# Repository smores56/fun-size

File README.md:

Fun Size
========

The Fun Size is an ergonomic keyboard PCB. With 32 to 36 keys, it uses Kailh hotswap sockets to
support Choc v1 switches, in addition to up to 4 EVQWGD001 horizontal rotary encoders.

The first version has had prototypes ordered for testing and depiction here using the
[gerber archive][./v1/fun-size.zip] saved in this repo. Once it arrives, pictures will be uploaded
here.

Check back later for QMK configuration to run your own.

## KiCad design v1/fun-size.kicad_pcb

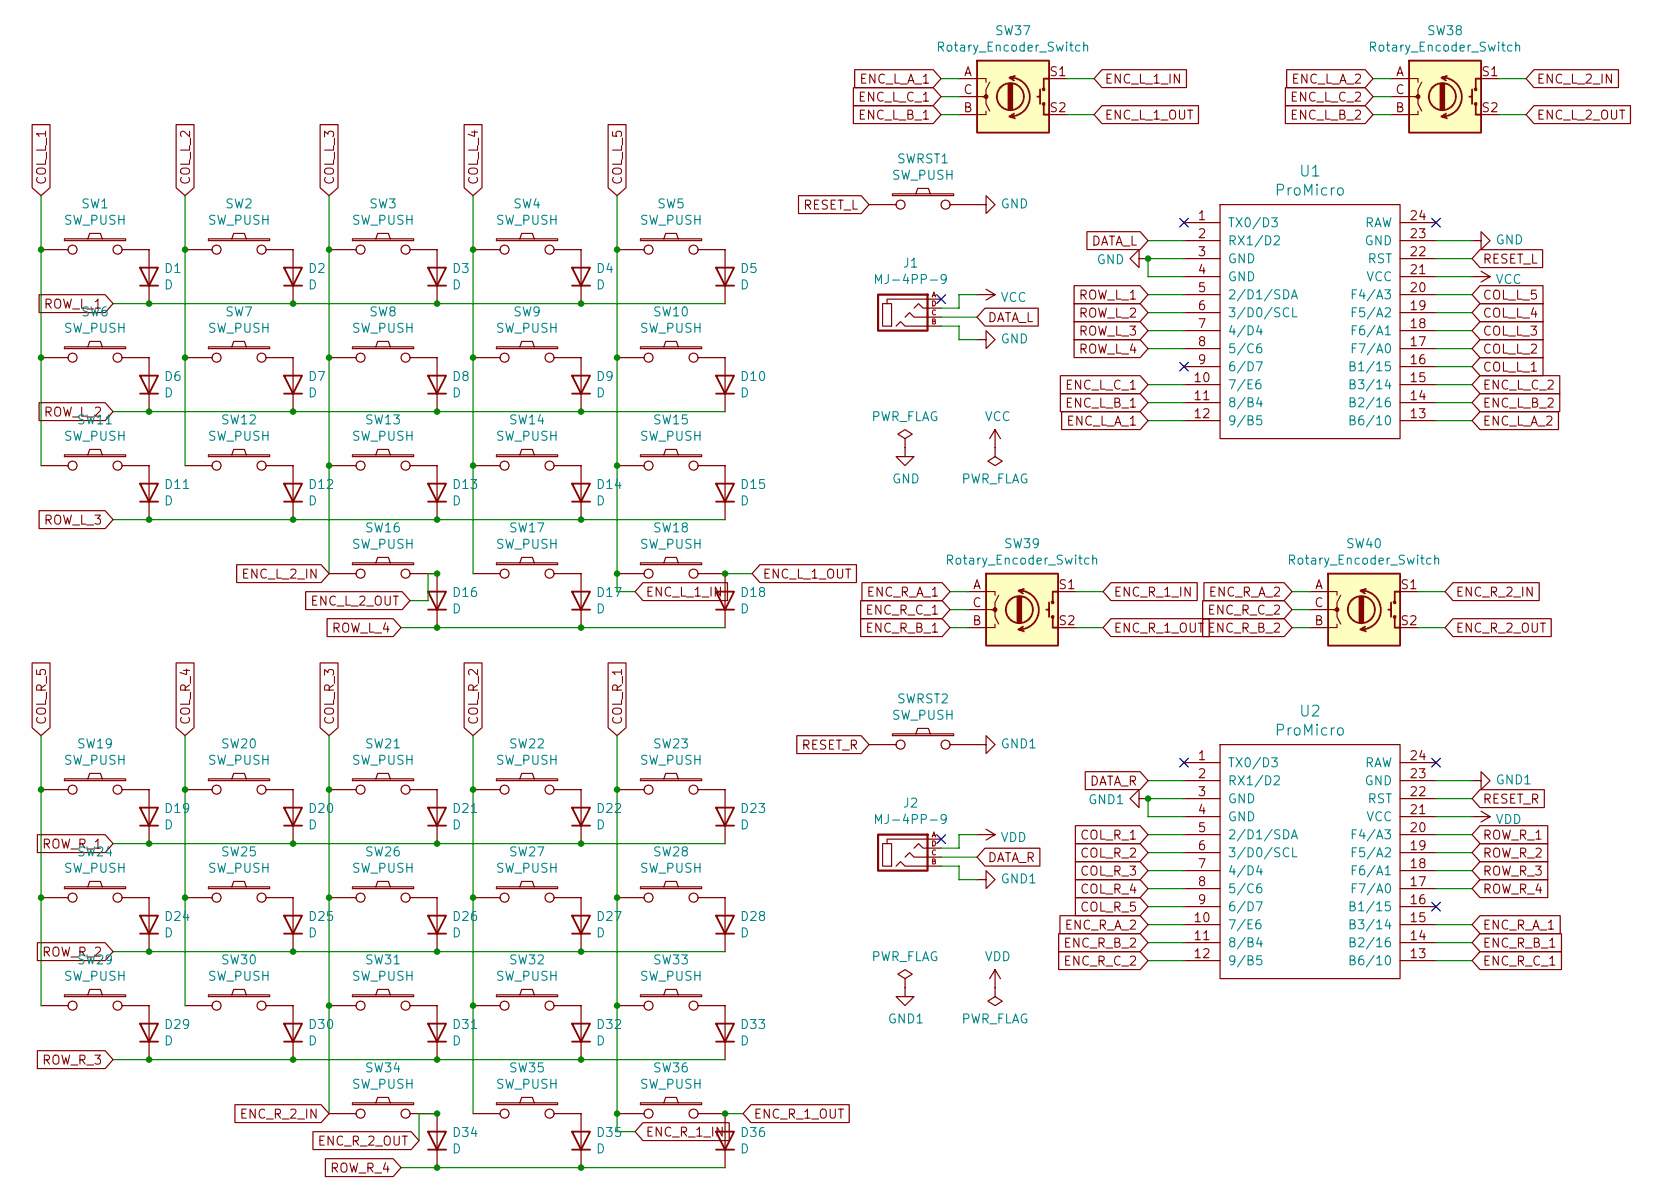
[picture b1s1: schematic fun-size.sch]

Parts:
D1, D2, D3, D4, D5, D6, D7, D8, D9, D10, D11, D12, D13, D14, D15, D16, D17, D18, D19, D20, D21, D22, D23, D24, D25, D26, D27, D28, D29, D30, D31, D32, D33, D34, D35, D36: D; D3_SMD_v2
J1, J2: MJ-4PP-9; MJ-4PP-9_1side
SW1, SW2, SW3, SW4, SW5, SW6, SW7, SW8, SW9, SW10, SW11, SW12, SW13, SW14, SW15, SW16, SW17, SW18, SW19, SW20, SW21, SW22, SW23, SW24, SW25, SW26, SW27, SW28, SW29, SW30, SW31, SW32, SW33, SW34, SW35, SW36: SW_PUSH; Kailh_socket_PG1350
SW37, SW38, SW39, SW40: Rotary_Encoder_Switch; RollerEncoder_Panasonic_EVQWGD001
SWRST1, SWRST2: SW_PUSH; ResetSW
U1, U2: ProMicro; ProMicro_v3

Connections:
COL_L_1: SW1.1, SW6.1, SW11.1, U1.16 (B1/15)
COL_L_2: SW2.1, SW7.1, SW12.1, U1.17 (F7/A0)
COL_L_3: SW3.1, SW8.1, SW13.1, SW16.1, SW38.S1, U1.18 (F6/A1)
COL_L_4: SW4.1, SW9.1, SW14.1, SW17.1, U1.19 (F5/A2)
COL_L_5: SW5.1, SW10.1, SW15.1, SW18.1, SW37.S1, U1.20 (F4/A3)
COL_R_1: SW23.1, SW28.1, SW33.1, SW36.1, SW39.S1, U2.5 (2/D1/SDA)
COL_R_2: SW22.1, SW27.1, SW32.1, SW35.1, U2.6 (3/D0/SCL)
COL_R_3: SW21.1, SW26.1, SW31.1, SW34.1, SW40.S1, U2.7 (4/D4)
COL_R_4: SW20.1, SW25.1, SW30.1, U2.8 (5/C6)
COL_R_5: SW19.1, SW24.1, SW29.1, U2.9 (6/D7)
DATA_L: J1.C, U1.2 (RX1/D2)
DATA_R: J2.C, U2.2 (RX1/D2)
ENC_L_1_OUT: D18.2 (A), SW18.2, SW37.S2
ENC_L_2_OUT: D16.2 (A), SW16.2, SW38.S2
ENC_L_A_1: SW37.A, U1.12 (9/B5)
ENC_L_A_2: SW38.A, U1.13 (B6/10)
ENC_L_B_1: SW37.B, U1.11 (8/B4)
ENC_L_B_2: SW38.B, U1.14 (B2/16)
ENC_L_C_1: SW37.C, U1.10 (7/E6)
ENC_L_C_2: SW38.C, U1.15 (B3/14)
ENC_R_1_OUT: D36.2 (A), SW36.2, SW39.S2
ENC_R_2_OUT: D34.2 (A), SW34.2, SW40.S2
ENC_R_A_1: SW39.A, U2.15 (B3/14)
ENC_R_A_2: SW40.A, U2.10 (7/E6)
ENC_R_B_1: SW39.B, U2.14 (B2/16)
ENC_R_B_2: SW40.B, U2.11 (8/B4)
ENC_R_C_1: SW39.C, U2.13 (B6/10)
ENC_R_C_2: SW40.C, U2.12 (9/B5)
GND: J1.B, SWRST1.2, U1.3 (GND), U1.4 (GND), U1.23 (GND)
GND1: J2.B, SWRST2.2, U2.3 (GND), U2.4 (GND), U2.23 (GND)
unnamed: D1.2 (A), SW1.2
unnamed: D2.2 (A), SW2.2
unnamed: D3.2 (A), SW3.2
unnamed: D4.2 (A), SW4.2
unnamed: D5.2 (A), SW5.2
unnamed: D6.2 (A), SW6.2
unnamed: D7.2 (A), SW7.2
unnamed: D8.2 (A), SW8.2
unnamed: D9.2 (A), SW9.2
unnamed: D10.2 (A), SW10.2
unnamed: D11.2 (A), SW11.2
unnamed: D12.2 (A), SW12.2
unnamed: D13.2 (A), SW13.2
unnamed: D14.2 (A), SW14.2
unnamed: D15.2 (A), SW15.2
unnamed: D17.2 (A), SW17.2
unnamed: D19.2 (A), SW19.2
unnamed: D20.2 (A), SW20.2
unnamed: D21.2 (A), SW21.2
unnamed: D22.2 (A), SW22.2
unnamed: D23.2 (A), SW23.2
unnamed: D24.2 (A), SW24.2
unnamed: D25.2 (A), SW25.2
unnamed: D26.2 (A), SW26.2
unnamed: D27.2 (A), SW27.2
unnamed: D28.2 (A), SW28.2
unnamed: D29.2 (A), SW29.2
unnamed: D30.2 (A), SW30.2
unnamed: D31.2 (A), SW31.2
unnamed: D32.2 (A), SW32.2
unnamed: D33.2 (A), SW33.2
unnamed: D35.2 (A), SW35.2
RESET_L: SWRST1.1, U1.22 (RST)
RESET_R: SWRST2.1, U2.22 (RST)
ROW_L_1: D1.1 (K), D2.1 (K), D3.1 (K), D4.1 (K), D5.1 (K), U1.5 (2/D1/SDA)
ROW_L_2: D6.1 (K), D7.1 (K), D8.1 (K), D9.1 (K), D10.1 (K), U1.6 (3/D0/SCL)
ROW_L_3: D11.1 (K), D12.1 (K), D13.1 (K), D14.1 (K), D15.1 (K), U1.7 (4/D4)
ROW_L_4: D16.1 (K), D17.1 (K), D18.1 (K), U1.8 (5/C6)
ROW_R_1: D19.1 (K), D20.1 (K), D21.1 (K), D22.1 (K), D23.1 (K), U2.20 (F4/A3)
ROW_R_2: D24.1 (K), D25.1 (K), D26.1 (K), D27.1 (K), D28.1 (K), U2.19 (F5/A2)
ROW_R_3: D29.1 (K), D30.1 (K), D31.1 (K), D32.1 (K), D33.1 (K), U2.18 (F6/A1)
ROW_R_4: D34.1 (K), D35.1 (K), D36.1 (K), U2.17 (F7/A0)
VCC: J1.D, U1.21 (VCC)
VDD: J2.D, U2.21 (VCC)

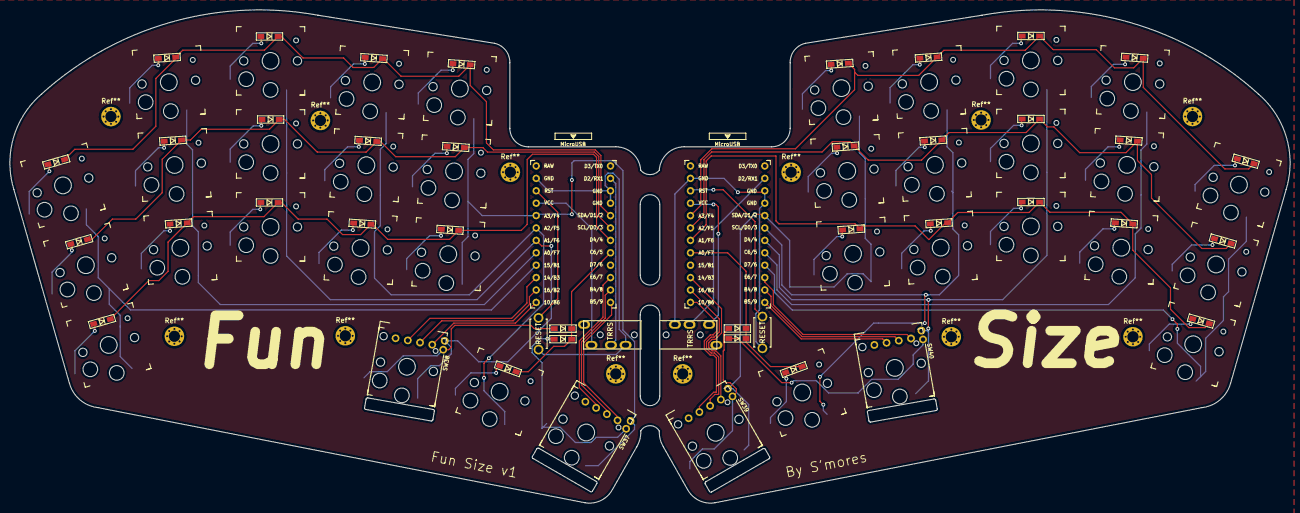
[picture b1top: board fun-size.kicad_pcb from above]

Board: 2 copper layers, 262.2 x 101.0 mm, 94 parts (0 on the bottom side), 74 nets.

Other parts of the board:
Ref**: Val**; M2_HOLE_v3
Ref**#2, Ref**#3, Ref**#4, Ref**#5, Ref**#6, Ref**#7, Ref**#8, Ref**#9, Ref**#10, Ref**#11, Ref**#12: Val**; M2_HOLE_v3

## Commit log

2021-06-23 Create routed layout
2021-06-23 finish PCB design v1
2021-06-24 add mounting holes for a case
2021-06-24 add gerber zip for JLC
2021-06-24 thicken bridges between halves
2021-06-24 add README
2021-06-24 finish README
2021-06-24 add MIT license
